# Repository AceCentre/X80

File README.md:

# X80

X80 is an Arduino-based multi-functional input/output device designed to be an interface between assistive technology inputs such as accessibility switches or specilist sensors and mainstream technology outputs, such as to a mobile phone or Augmentative and Alternative Communication (AAC) device.

An X80 can be preprogrammed and repurposed to perform a different function. It's built around the Adafruit Feather, generally the nrf82540 Express. It's essentially a Feather Wing for Assistive Technology (AT).

There are a couple of smilar projects:

https://github.com/google/mimosa

https://github.com/asterics/FABI

The PCB is still a work in progress but it is designed to have:

* Switch inputs via 3.5mm jack
* switch outputs via 3.5mm jack (simulates a switch press as an input into an Assistive Technology device)
* DB9 connector designed to accomodate devices meeting the TRACE SET Standard often used with accessibility input devices (https://park.org/Guests/Trace/pavilion/setdoc1.htm)
* buzzer
* potentiometer
* on/off switch

There are a few differences between the prototype versions:

## Version 4

The funtionality has been split into two boards:

* X80 Standard (designed for Adafruit ItsyBitsy nrf52840 https://www.adafruit.com/product/4481)
* X80 Power (required for LIPO battery as this board includes the chargin circuit)

### X80 Standard

* Majority surface mount components
* 4 switch inputs (5 with splitter cable on one port)
* 4 switch outputs
* One switch 'pass through' (one switch input will still control on switch output without power)
* buzzer
* setting potentiometer
* header for connecting X80 Power or wiring direct to board)

### X80 Power

* JST connector for LIPO battery
* DB9 connector for connecting external peripherals
* will allow space in enclosure for LIPO battery

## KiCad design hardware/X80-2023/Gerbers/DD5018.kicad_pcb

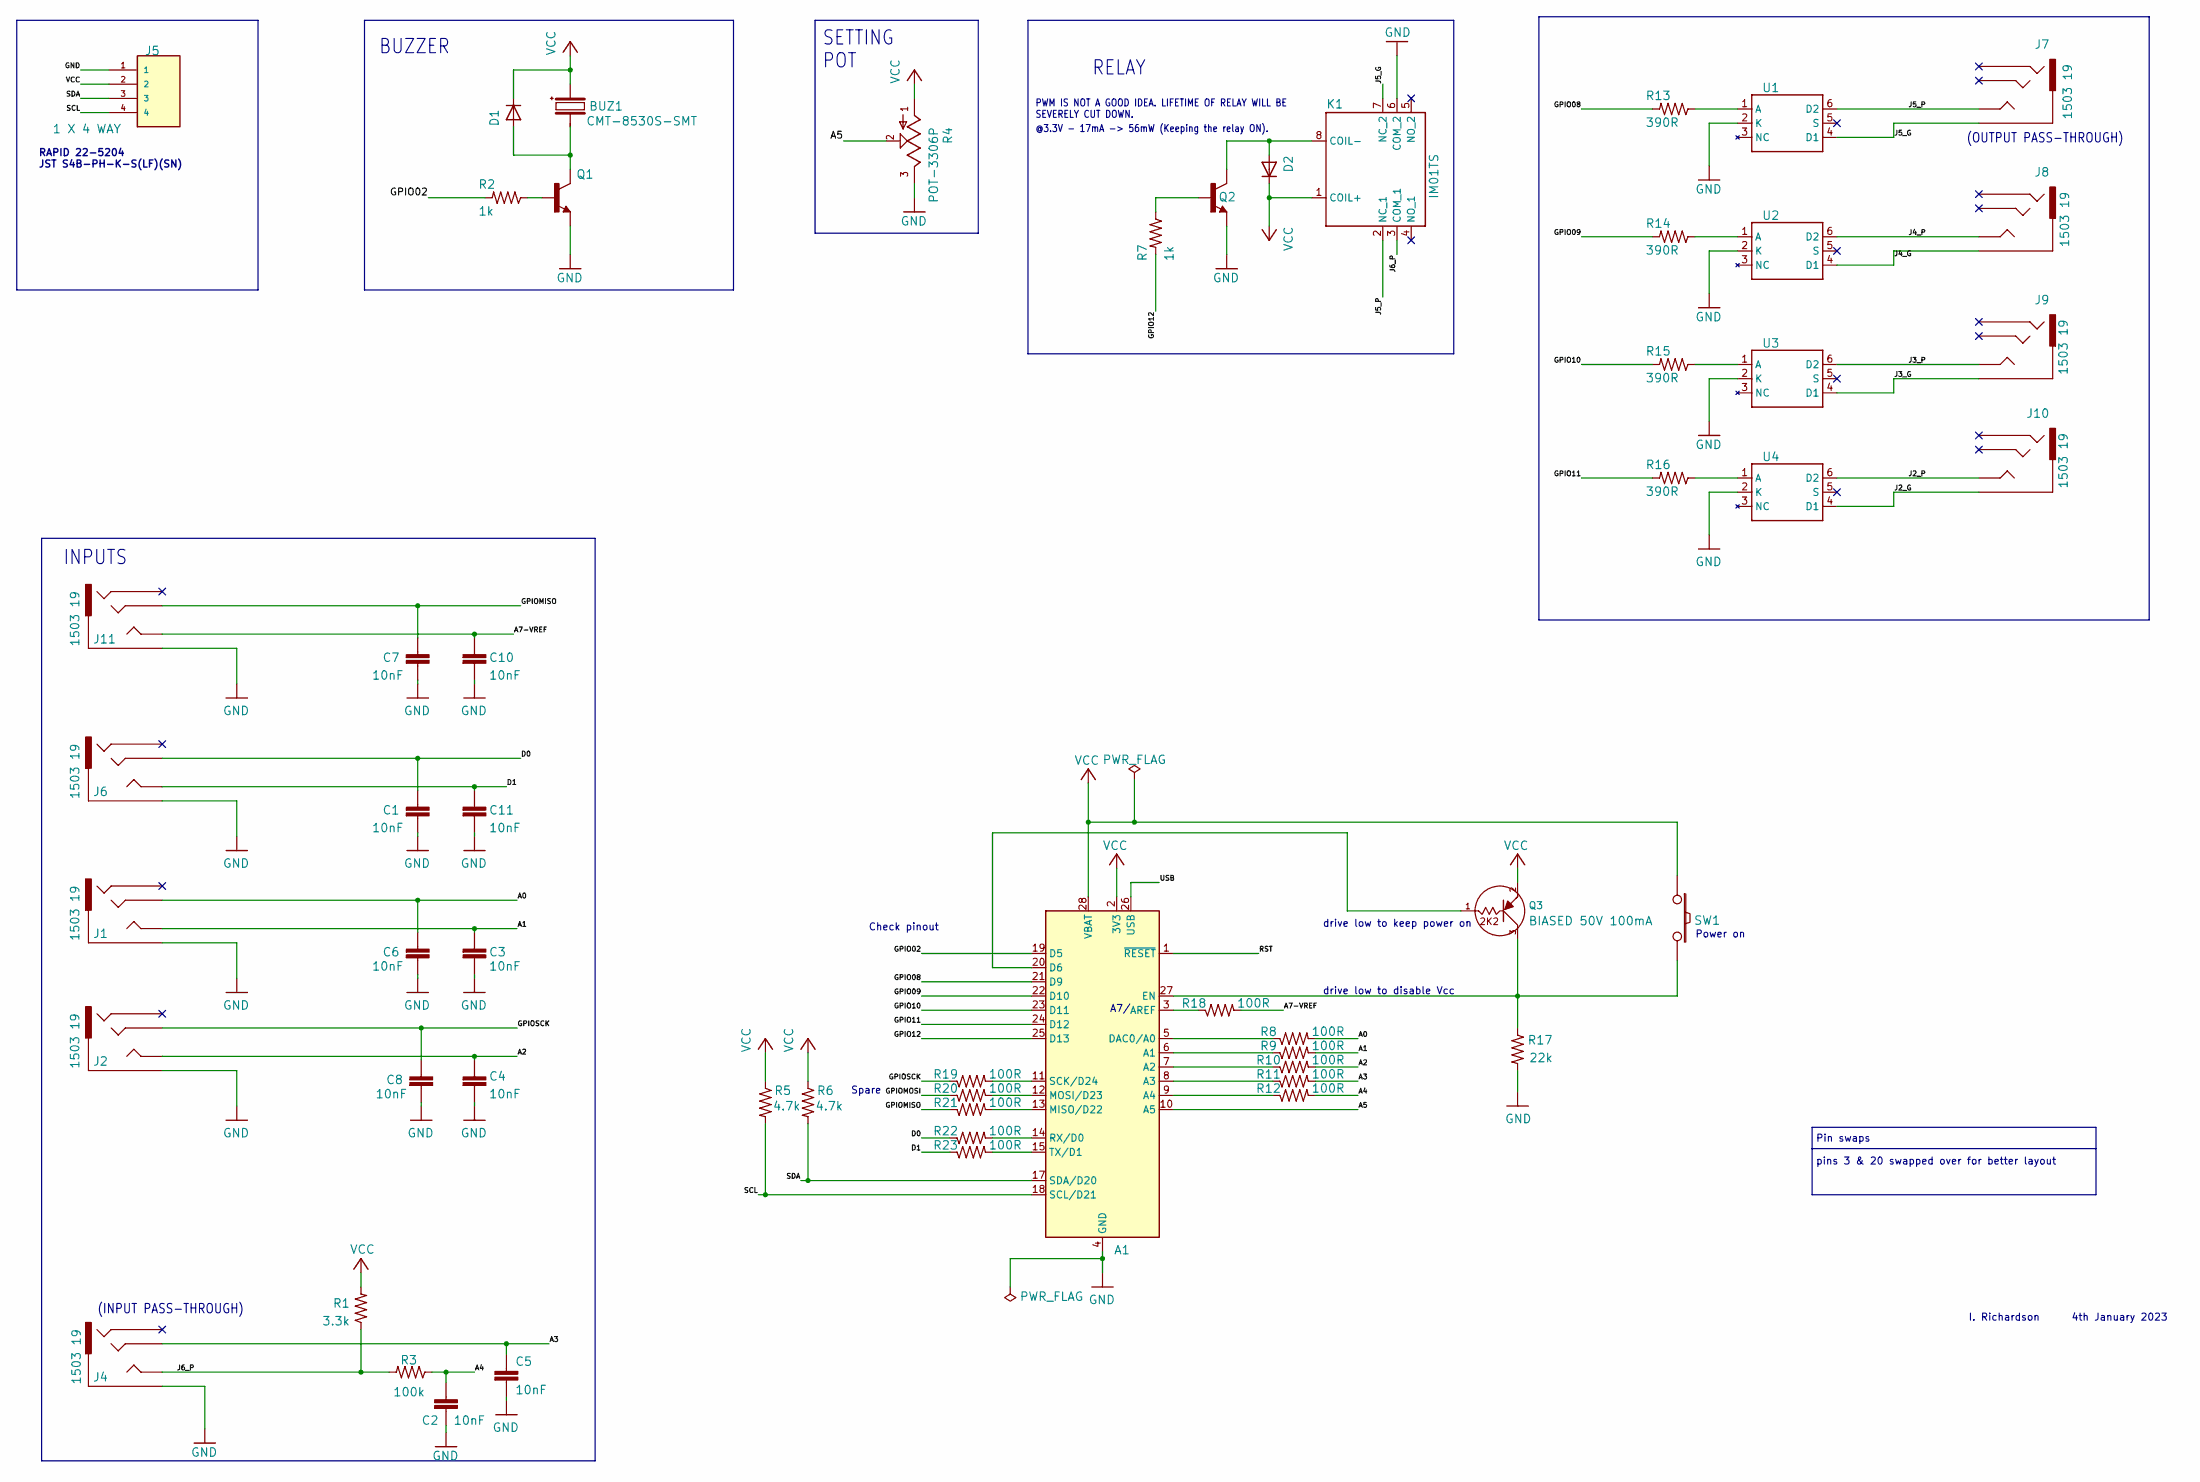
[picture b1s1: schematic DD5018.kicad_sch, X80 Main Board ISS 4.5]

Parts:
A1: Adafruit_Feather_M0_Basic_Proto; Adafruit_Feather
BUZ1: CMT-8530S-SMT; CMT8530SSMTTR
C1, C2, C3, C4, C5, C6, C7, C8, C10, C11: 10nF; CAPC1608X85
D1, D2: DIODE-SOD-123; SOD-123
J1, J2, J4, J6, J7, J8, J9, J10, J11: 1503 19; 1503-19
J5: 1 X 4 WAY; JST_S4B-PH-K-S(LF)(SN)
K1: IM01TS; IM03TS114620378
Q1, Q2: NPN-SOT-23; SOT-23
Q3: PNP-BIASED-2K2; SOT23-MMBT4401B; Part No MMUN2135LT1G
R1: 3.3k; R0603
R2, R7: 1k; R0603
R3: 100k; R0603
R4: POT-3306P; 3306P1103
R5, R6: 4.7k; R0603
R8, R9, R10, R11, R12, R18, R19, R20, R21, R22, R23: 100R; R0603
R13, R14, R15, R16: 390R; R0603
R17: 22k; R0603
SW1: SW_mini_SMT; DTSM-32S-B; Part No DTSM-32S-B
U1, U2, U3, U4: LH1500AT; DIP762W47P254L880H410Q6N

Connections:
/A0: C6.1, J1.3, R8.1
/A1: C3.1, J1.4, J1.5 (4), R9.1
/A2: C4.1, J2.4, J2.5 (4), R10.1
/A3: C5.1, J4.3, R11.1
/A4: C2.1, R3.2, R12.1
/A5: A1.10 (A5), R4.2
/A7-VREF: C10.1, J11.4, J11.5 (4), R18.1
/D0: C1.1, J6.3, R22.2
/D1: C11.1, J6.4, J6.5 (4), R23.2
/GPIO02: A1.19 (D5), R2.1
/GPIO08: A1.21 (D9), R13.1
/GPIO09: A1.22 (D10), R14.1
/GPIO10: A1.23 (D11), R15.1
/GPIO11: A1.24 (D12), R16.1
/GPIO12: A1.25 (D13), R7.1
/GPIOMISO: C7.1, J11.3, R21.2
/GPIOMOSI: R20.2
/GPIOSCK: C8.1, J2.3, R19.2
/J2_G: J10.1, U4.4 (D1)
/J2_P: J10.4, J10.5 (4), U4.6 (D2)
/J3_G: J9.1, U3.4 (D1)
/J3_P: J9.4, J9.5 (4), U3.6 (D2)
/J4_G: J8.1, U2.4 (D1)
/J4_P: J8.4, J8.5 (4), U2.6 (D2)
/J5_G: J7.1, K1.7 (NC_2), U1.4 (D1)
/J5_P: J7.4, J7.5 (4), K1.2 (NC_1), U1.6 (D2)
/J6_P: J4.4, J4.5 (4), K1.3 (COM_1), R1.2, R3.1
/RST: A1.1 (~RESET)
/SCL: A1.18 (SCL/D21), J5.4, R5.1
/SDA: A1.17 (SDA/D20), J5.3, R6.1
/USB: A1.26 (USB)
GND: A1.4 (GND), A1.16 (GND), C1.2, C2.2, C3.2, C4.2, C5.2, C6.2, C7.2, C8.2, C10.2, C11.2, J1.1, J2.1, J4.1, J5.1, J6.1, J11.1, K1.6 (COM_2), Q1.E, Q2.E, R4.3, R17.1, U1.2 (K), U2.2 (K), U3.2 (K), U4.2 (K)
unnamed: A1.3 (AREF), R18.2
unnamed: A1.5 (DAC0/A0), R8.2
unnamed: A1.6 (A1), R9.2
unnamed: A1.7 (A2), R10.2
unnamed: A1.8 (A3), R11.2
unnamed: A1.9 (A4), R12.2
unnamed: A1.11 (SCK/D24), R19.1
unnamed: A1.12 (MOSI/D23), R20.1
unnamed: A1.13 (MISO/D22), R21.1
unnamed: A1.14 (RX/D0), R22.1
unnamed: A1.15 (TX/D1), R23.1
unnamed: A1.20 (D6), Q3.1
unnamed: A1.27 (EN), Q3.3, R17.2, SW1.2
unnamed: BUZ1.3 (-), D1.A, Q1.C
unnamed: D2.A, K1.8 (COIL-), Q2.C
unnamed: Q1.B, R2.2
unnamed: Q2.B, R7.2
unnamed: R13.2, U1.1 (A)
unnamed: R14.2, U2.1 (A)
unnamed: R15.2, U3.1 (A)
unnamed: R16.2, U4.1 (A)
VCC: A1.2 (3V3), A1.28 (VBAT), BUZ1.2 (+), D1.C, D2.C, J5.2, K1.1 (COIL+), Q3.2, R1.1, R4.1, R5.2, R6.2, SW1.1

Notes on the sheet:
RELAY
Spare
PWM IS NOT A GOOD IDEA. LIFETIME OF RELAY WILL BE SEVERELY CUT DOWN.
(OUTPUT PASS-THROUGH)
(INPUT PASS-THROUGH)
4th January 2023
Power on
I. Richardson
RAPID 22-5204 JST S4B-PH-K-S(LF)(SN)
INPUTS
A7/
@3.3V - 17mA -> 56mW (Keeping the relay ON).
drive low to keep power on
drive low to disable Vcc
BUZZER
SETTING POT
Check pinout
Pin swaps pins 3 & 20 swapped over for better layout

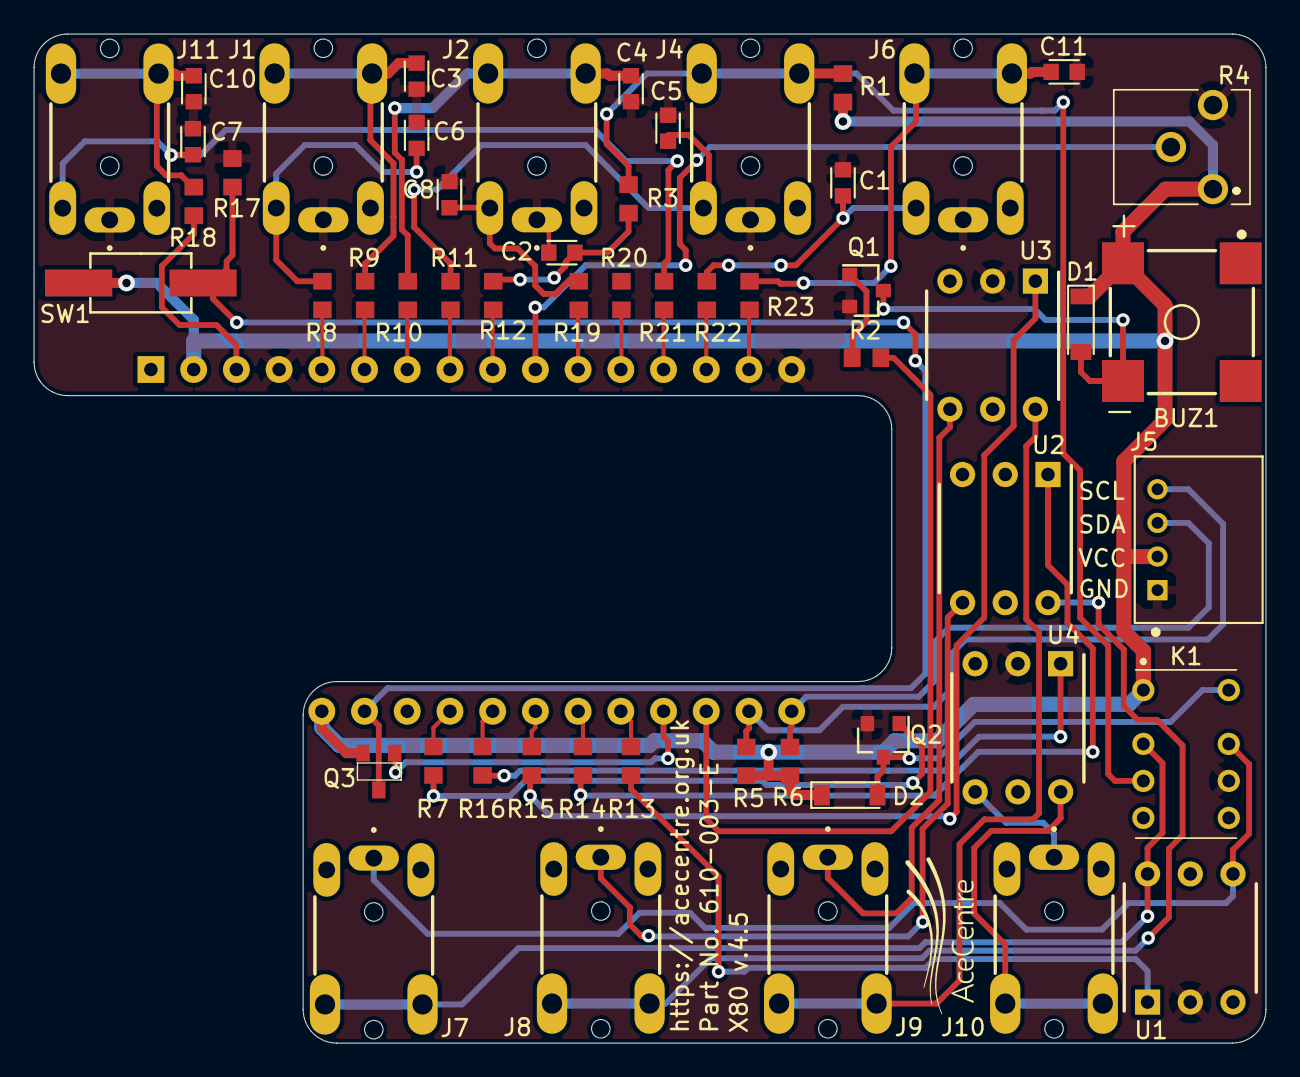
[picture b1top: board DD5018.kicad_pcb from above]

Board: 2 copper layers, 73.2 x 60.0 mm, 56 parts (1 on the bottom side), 51 nets.

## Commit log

2020-10-25 Multi starter file
2020-10-25 Create LICENSE
2020-10-26 Added simpler sketch testing switch output
2021-01-18 Create iOS-test.py
    Opens Photos.
2021-03-10 Folder structure updated for current versions
2021-08-08 Included Version 4
2021-08-08 Added PCB schematic pdf
2021-08-08 Corrected model number
2022-01-24 Changes made to hardware enclosures and folder structure
    Removed references to previous versions. Changed file structure to make easier to follow. Added example code.
2022-01-24 Lens and Mounting plate moved to parts folder
2022-02-09 adding other code & renaming folders
2022-02-09 adding circuitPy demo
2022-02-10 Enclosure updated
2022-02-10 Added switch switcher and blink
2022-06-14 Add v1 of circuit python
2022-06-14 Fix readme
2022-06-14 Add another longer term
2022-06-17 Python switcher now outputs
2022-06-17 Final version of switch switcher
2022-07-14 Ignore mac files
2022-07-14 Upload new switcher
2022-07-15 Add bluetooth switcher
2022-08-17 Add five switch remote
2022-08-22 Add a keyboard commad to do CTRL + TAB
2023-01-25 Adding Wireless Switch demo.
    NB: This won't work on an X80 right now. This works on any nrf52840 chipset and note to add LED and Switches for the right pins.
2023-01-25 adding in to-do
2023-01-25 fixing done items
2023-01-25 add a bit more info
2023-01-26 sleep functionality added
    If there is no switch presses for defined amount of time then the board goes into deep sleep.
    This amount of time can be adjusted with "sleep_timeout" variable at line 8.
    Default value is 5 seconds.
    To wake up boards it's needed to press the switch .
    First press will be for board wake up and after built in led will turn on board will be ready to transmit data.
    It takes about 1 second.
2023-01-26 adding words
2023-01-28 adding in start of demo python code
2023-01-28 Including battery details
2023-01-29 adding another issue ref
2023-02-02 adding test code
2023-02-06 deals with dropped packets
2023-02-09 deals with holding down the key
2023-02-13 ading new python code
2023-02-13 removing old test code
2023-02-13 fixing to-dos
2023-02-13 adding boards
2023-02-14 adding redirect warning
2023-02-23 BOM and schematic
2023-02-23 adding raw gerbers files
2023-03-20 adding some images
2024-03-25 adding presstester
2024-03-25 ahh pulser
